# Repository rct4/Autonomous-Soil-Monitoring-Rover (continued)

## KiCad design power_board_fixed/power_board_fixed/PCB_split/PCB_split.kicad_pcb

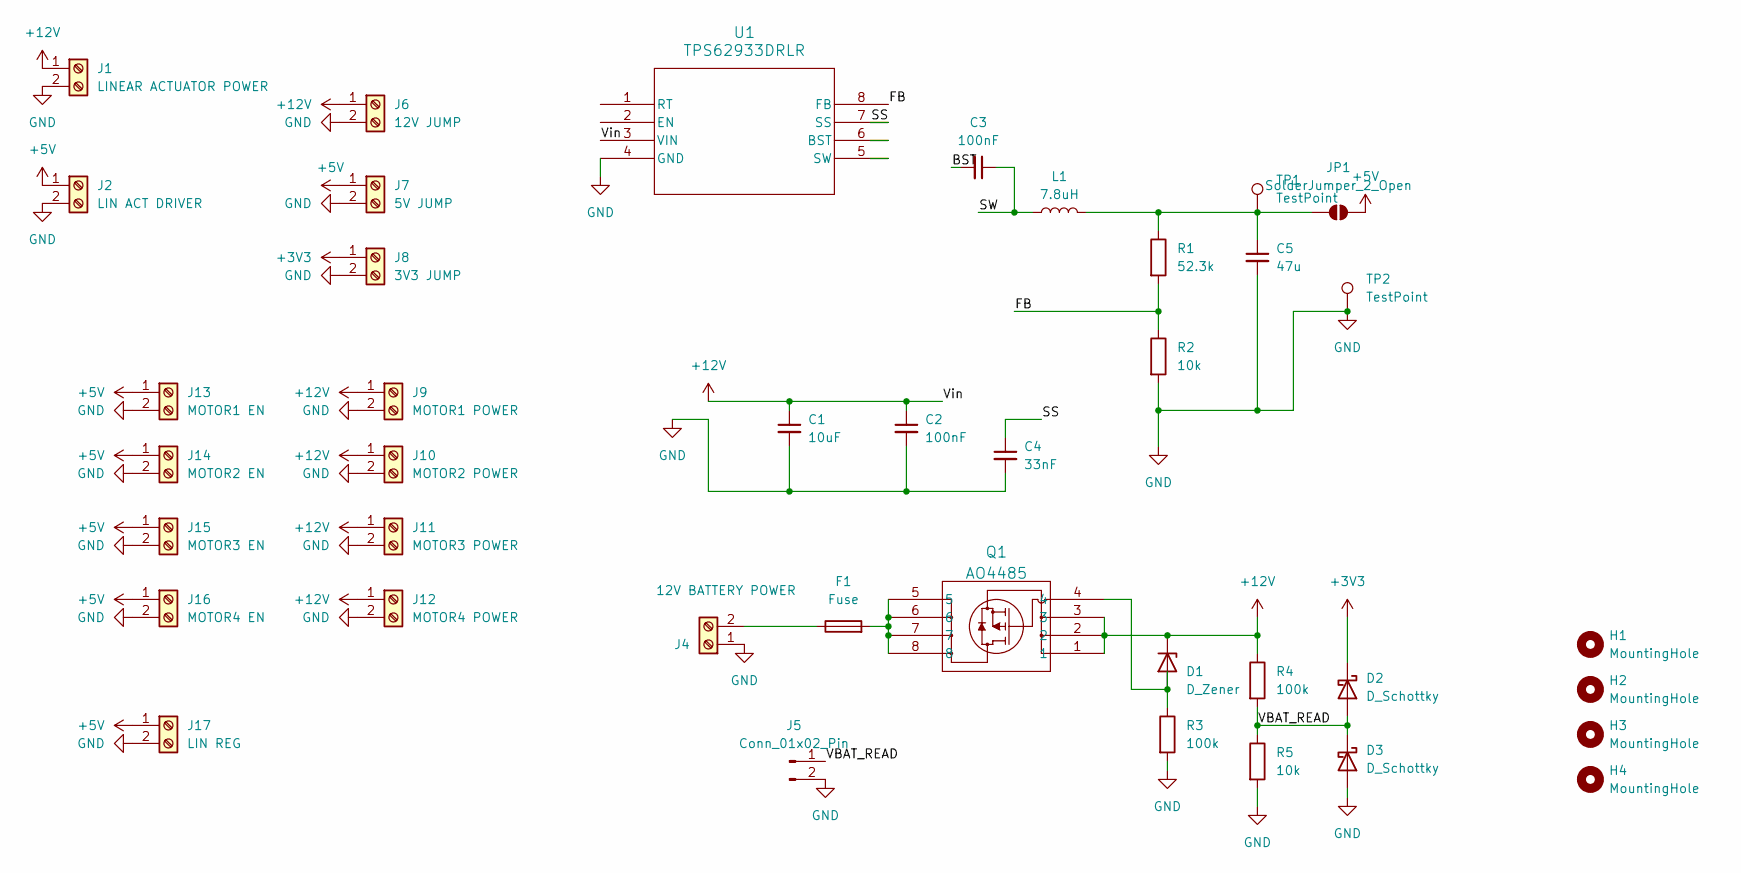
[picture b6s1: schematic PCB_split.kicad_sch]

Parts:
C1: 10uF; C_0805_2012Metric_Pad1.18x1.45mm_HandSolder
C2, C3: 100nF; C_0805_2012Metric_Pad1.18x1.45mm_HandSolder
C4: 33nF; C_0805_2012Metric_Pad1.18x1.45mm_HandSolder
C5: 47u; C_0805_2012Metric_Pad1.18x1.45mm_HandSolder
D1: D_Zener; D_SOD-123
D2, D3: D_Schottky; TSOT-23_HandSoldering
F1: Fuse; Fuseholder_Littelfuse_Nano2_154x
H1, H2, H3, H4: MountingHole; MountingHole_3.2mm_M3
J1: LINEAR ACTUATOR POWER; TerminalBlock_Phoenix_MKDS-1,5-2-5.08_1x02_P5.08mm_Horizont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
J2: LIN ACT DRIVER; TerminalBlock_Phoenix_MKDS-1,5-2-5.08_1x02_P5.08mm_Horizont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
J4: 12V BATTERY POWER; TerminalBlock_Phoenix_MKDS-1,5-2-5.08_1x02_P5.08mm_Horizont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
J5: Conn_01x02_Pin; TerminalBlock_Phoenix_MKDS-1,5-2-5.08_1x02_P5.08mm_Horizont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
J6: 12V JUMP; TerminalBlock_Phoenix_MKDS-1,5-2-5.08_1x02_P5.08mm_Horizont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
J7: 5V JUMP; TerminalBlock_Phoenix_MKDS-1,5-2-5.08_1x02_P5.08mm_Horizont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
J8: 3V3 JUMP; TerminalBlock_Phoenix_MKDS-1,5-2-5.08_1x02_P5.08mm_Horizont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
J9: MOTOR1 POWER; TerminalBlock_Phoenix_MKDS-1,5-2-5.08_1x02_P5.08mm_Horizont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
J10: MOTOR2 POWER; TerminalBlock_Phoenix_MKDS-1,5-2-5.08_1x02_P5.08mm_Horizont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
J11: MOTOR3 POWER; TerminalBlock_Phoenix_MKDS-1,5-2-5.08_1x02_P5.08mm_Horizont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
J12: MOTOR4 POWER; TerminalBlock_Phoenix_MKDS-1,5-2-5.08_1x02_P5.08mm_Horizont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
J13: MOTOR1 EN; TerminalBlock_Phoenix_MKDS-1,5-2-5.08_1x02_P5.08mm_Horizont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
J14: MOTOR2 EN; TerminalBlock_Phoenix_MKDS-1,5-2-5.08_1x02_P5.08mm_Horizont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
J15: MOTOR3 EN; TerminalBlock_Phoenix_MKDS-1,5-2-5.08_1x02_P5.08mm_Horizont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
J16: MOTOR4 EN; TerminalBlock_Phoenix_MKDS-1,5-2-5.08_1x02_P5.08mm_Horizont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
J17: LIN REG; TerminalBlock_Phoenix_MKDS-1,5-2-5.08_1x02_P5.08mm_Horizont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
JP1: SolderJumper_2_Open; SolderJumper-2_P1.3mm_Open_RoundedPad1.0x1.5mm
L1: 7.8uH; L_0201_0603Metric_Pad0.64x0.40mm_HandSolder
Q1: AO4485; SO8SOP-8L_AOS
R1: 52.3k; R_0805_2012Metric_Pad1.20x1.40mm_HandSolder
R2, R5: 10k; R_0805_2012Metric_Pad1.20x1.40mm_HandSolder
R3, R4: 100k; R_0805_2012Metric_Pad1.20x1.40mm_HandSolder
TP1, TP2: TestPoint; TestPoint_Pad_2.5x2.5mm
U1: TPS62933DRLR; SOT5X3-8_DRL_TEX

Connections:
+3V3: D2.1 (K), J8.1
+5V: J2.1, J7.1, J13.1, J14.1, J15.1, J16.1, J17.1, JP1.2 (B)
+12V: C1.1, C2.1, D1.1 (K), J1.1, J6.1, J9.1, J10.1, J11.1, J12.1, Q1.1, Q1.2, Q1.3, R4.1, U1.3 (VIN)
/BST: C3.2
/FB: R1.2, R2.1, U1.8 (FB)
/SS: C4.1, U1.7 (SS)
/SW: C3.1, L1.1
/VBAT_READ: D2.2 (A), D3.1 (K), J5.1, R4.2, R5.1
GND: C1.2, C2.2, C4.2, C5.2, D3.2 (A), J1.2, J2.2, J4.1, J5.2, J6.2, J7.2, J8.2, J9.2, J10.2, J11.2, J12.2, J13.2, J14.2, J15.2, J16.2, J17.2, R2.2, R3.2, R5.2, TP2.1, U1.4 (GND)
unnamed: D1.2 (A), Q1.4, R3.1
unnamed: F1.2, Q1.5, Q1.6, Q1.7, Q1.8
unnamed: F1.1, J4.2
unnamed: C5.1, JP1.1 (A), L1.2, R1.1, TP1.1

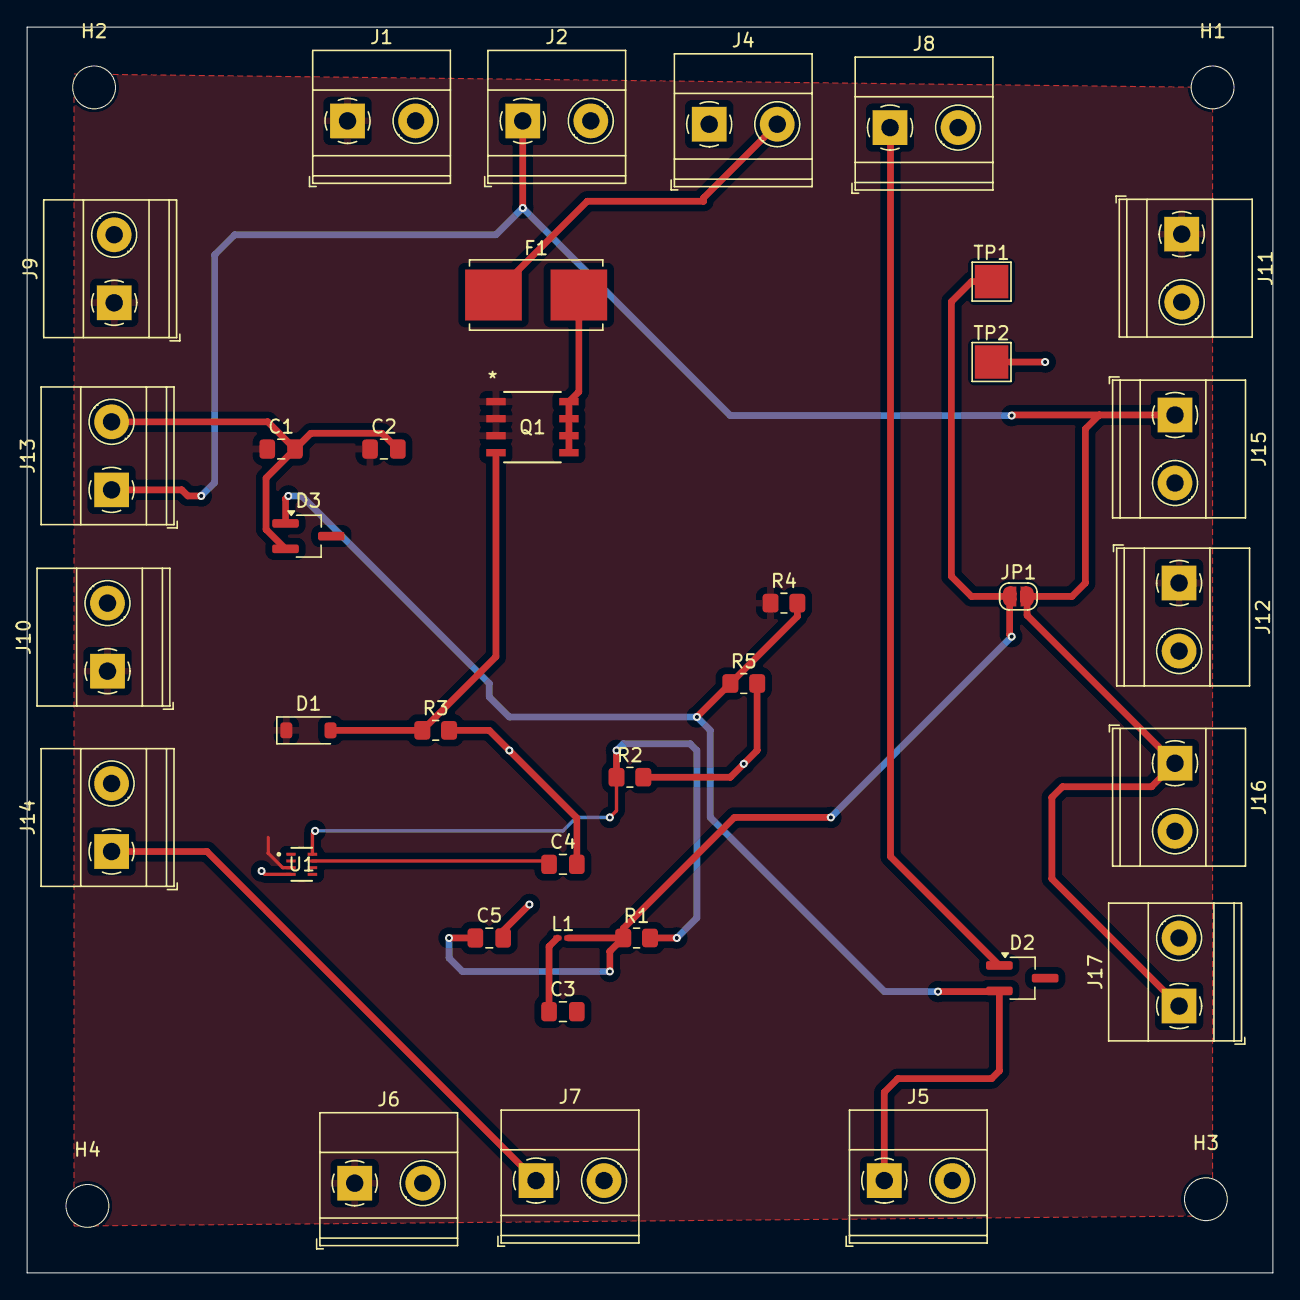
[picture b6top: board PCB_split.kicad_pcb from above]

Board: 2 copper layers, 93.0 x 93.0 mm, 40 parts (0 on the bottom side), 12 nets.

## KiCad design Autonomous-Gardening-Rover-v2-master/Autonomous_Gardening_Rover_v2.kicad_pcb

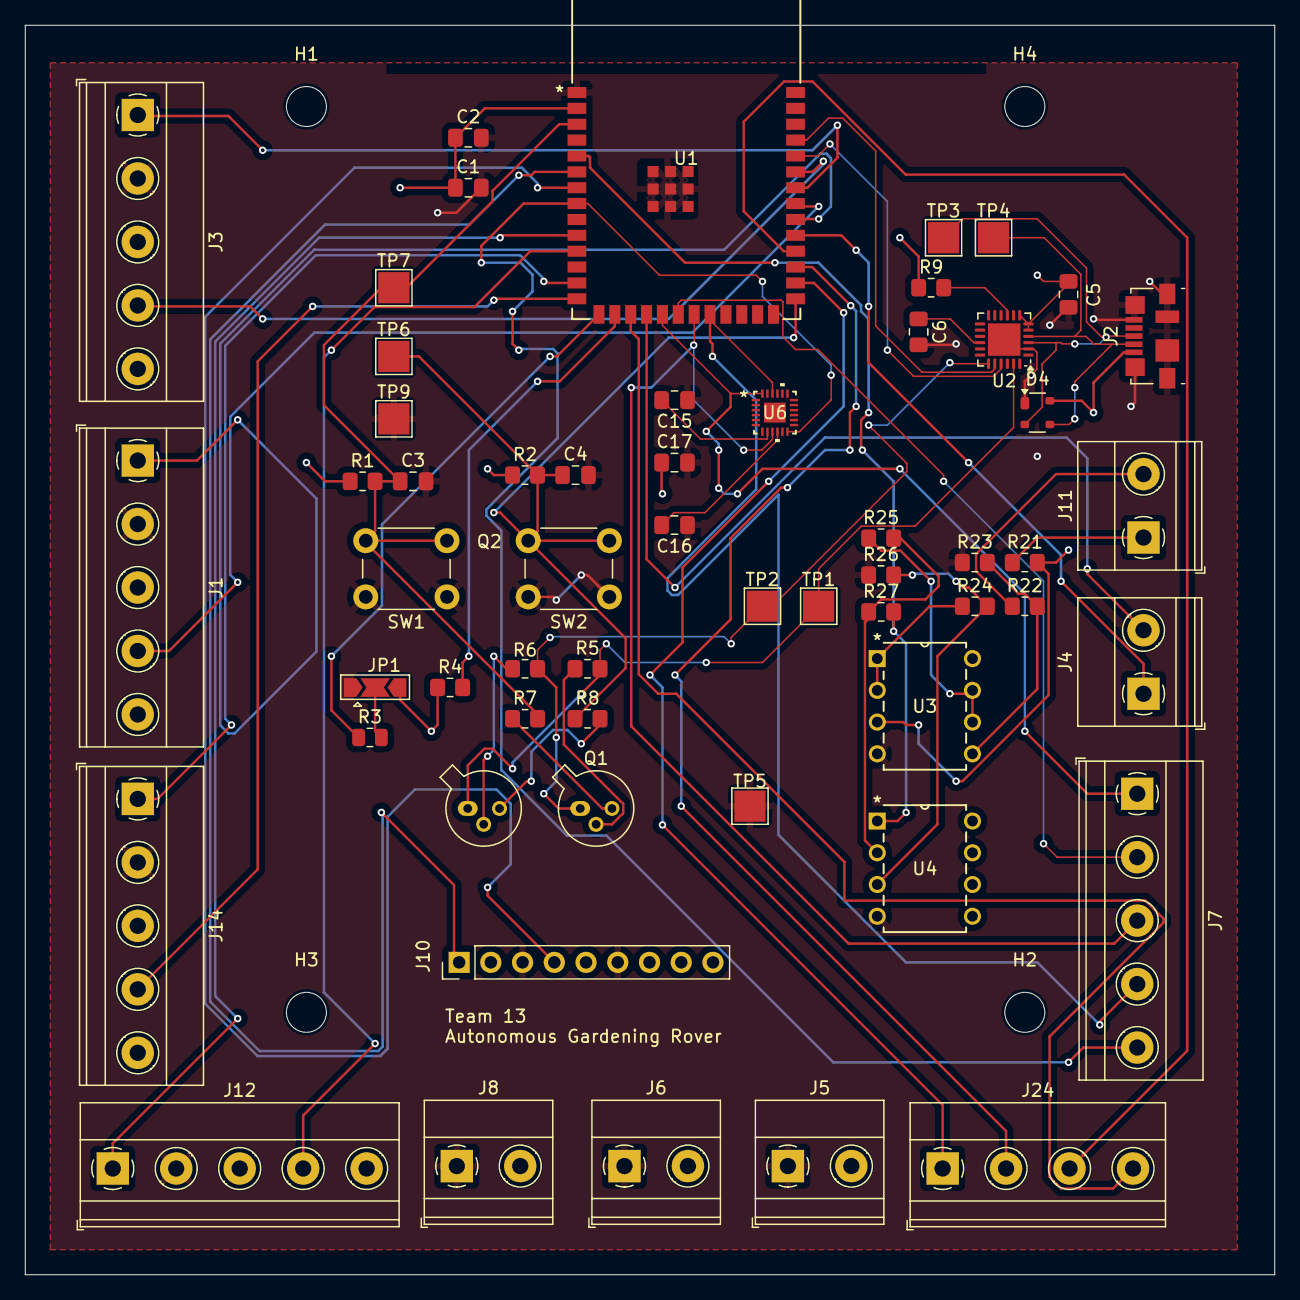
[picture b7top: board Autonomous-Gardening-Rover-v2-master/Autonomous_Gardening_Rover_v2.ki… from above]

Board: 6 copper layers, 100.0 x 100.0 mm, 61 parts (0 on the bottom side), 51 nets.

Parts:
C1: 10 uF; C_0805_2012Metric_Pad1.18x1.45mm_HandSolder
C2: 100 uF; C_0805_2012Metric_Pad1.18x1.45mm_HandSolder
C3, C4: 1 uF; C_0805_2012Metric_Pad1.18x1.45mm_HandSolder
C5: 10uF; C_0805_2012Metric_Pad1.18x1.45mm_HandSolder
C6: 4.7uF; C_0805_2012Metric_Pad1.18x1.45mm_HandSolder
C15: 10nf; C_0805_2012Metric_Pad1.18x1.45mm_HandSolder
C16, C17: 0.1uf; C_0805_2012Metric_Pad1.18x1.45mm_HandSolder
D4: SP0503BAHT; SOT-143
H1, H2, H3, H4: MountingHole; MountingHole_3.2mm_M3
J1, J3, J12, J14: Conn_01x05_Pin; TerminalBlock_Phoenix_MKDS-1,5-5-5.08_1x05_P5.08mm_Horizont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
J2: USB_B_Micro; USB_Micro-B_Molex_47346-0001
J4: LINEAR ACTUATOR SIGNAL; TerminalBlock_Phoenix_MKDS-1,5-2-5.08_1x02_P5.08mm_Horizont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
J5, J6, J8: Screw_Terminal_01x02; TerminalBlock_Phoenix_MKDS-1,5-2-5.08_1x02_P5.08mm_Horizont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
J7: MPU SIGNAL; TerminalBlock_Phoenix_MKDS-1,5-5-5.08_1x05_P5.08mm_Horizont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
J10: SENSORS; PinHeader_1x09_P2.54mm_Vertical
J11: Conn_01x02_Socket; TerminalBlock_Phoenix_MKDS-1,5-2-5.08_1x02_P5.08mm_Horizont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
J24: UWB SIGNAL; TerminalBlock_Phoenix_MKDS-1,5-4-5.08_1x04_P5.08mm_Horizont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
JP1: SolderJumper_3_Open; SolderJumper-3_P2.0mm_Open_TrianglePad1.0x1.5mm
Q1, Q2: BC107; TO-18-3
R1, R2: 100k; R_0805_2012Metric_Pad1.20x1.40mm_HandSolder
R3: 1k; R_0805_2012Metric
R4: 1k; R_0805_2012Metric_Pad1.20x1.40mm_HandSolder
R5, R6, R7, R8: 10k; R_0805_2012Metric_Pad1.20x1.40mm_HandSolder
R9: 4.7k; R_0805_2012Metric_Pad1.20x1.40mm_HandSolder
R21, R22: 100K; R_0805_2012Metric_Pad1.20x1.40mm_HandSolder
R23: 10M; R_0805_2012Metric_Pad1.20x1.40mm_HandSolder
R24, R25, R26, R27: 1K; R_0805_2012Metric_Pad1.20x1.40mm_HandSolder
SW1, SW2: SW_Push; SW_PUSH_6mm_H5mm
TP1, TP2, TP3, TP4, TP5: TestPoint; TestPoint_Pad_2.5x2.5mm
TP6: TEST GPIO0_STRAPPING; TestPoint_Pad_2.5x2.5mm
TP7: TEST CHIP_PU; TestPoint_Pad_2.5x2.5mm
TP9: TEST GND; TestPoint_Pad_2.5x2.5mm
U1: ESP32-S3-WROOM-1; ESP32-S3-WROOM-1_EXP
U2: CP2104; QFN-24-1EP_4x4mm_P0.5mm_EP2.6x2.6mm
U3, U4: LM358; P8
U6: MPU-6500; QFN24_3X3X0P9_IVS

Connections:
+3V3: C1.1, C2.1, C5.1, C15.2, C17.1, J8.2, J10.2, J10.5, JP1.3 (B), R1.1, R2.1, R4.1, R9.1, R21.2, U1.2 (3V3), U2.5 (VIO), U2.6 (VDD), U2.7 (REGIN), U3.3 (+), U3.8 (V+), U4.8 (V+), U6.8 (VDDIO), U6.13 (VDD)
+5V: D4.4 (K), J1.3, J2.1 (VBUS), J3.3, J6.2, J12.3, J14.3
+12V: J1.5, J3.5, J5.2, J12.5, J14.5
/CHIP_PU: C3.1, R1.2, R7.2, SW1.2, TP7.1, U1.3 (EN)
/D+: D4.2 (K), J2.3 (D+), TP3.1, U2.3 (D+)
/D-: D4.3 (K), J2.2 (D-), TP4.1, U2.4 (D-)
/DTR: Q2.1 (E), R5.2, TP1.1, U2.23 (~DTR)
/GPIO0_STRAPPING: C4.1, R2.2, R8.1, SW2.2, TP6.1, U1.27 (IO0)
/GPIO3_STRAPPING: R3.1, U1.15 (IO3)
/GPIO46_STRAPPING: R4.2, U1.16 (IO46)
/Input_Probe_1: J11.1, R21.1
/Input_Probe_2: J11.2, R22.1
/LINACT+: J4.1, U1.31 (IO38)
/LINACT-: J4.2, U1.18 (IO10)
/MOTOR1FG: J12.4, U1.11 (IO18)
/MOTOR1PWM: J12.1, U1.10 (IO17)
/MOTOR2FG: J14.4, U1.14 (IO20)
/MOTOR2PWM: J14.1, U1.13 (IO19)
/MOTOR3FG: J1.4, U1.33 (IO40)
/MOTOR3PWM: J1.1, U1.32 (IO39)
/MOTOR4FG: J3.4, U1.35 (IO42)
/MOTOR4PWM: J3.1, U1.34 (IO41)
/MPUCLK: J7.2, U1.20 (IO12), U6.23 (SCL/SCLK)
/MPUCS: J7.4, U1.22 (IO14), U6.22 (nCS)
/MPUINT: J7.5, U1.8 (IO15), U6.12 (INT)
/MPUMISO: J7.3, U1.21 (IO13), U6.9 (SDO/ADO)
/MPUMOSI: J7.1, U1.19 (IO11), U6.24 (SDA/SDI)
/Moisture_Sensor_Output: R27.2, U1.5 (IO5), U4.1
/RTS: Q1.1 (E), R6.2, TP2.1, U2.19 (~RTS)
/RXD: U1.37 (TXD0), U2.20 (RXD)
/TXD: U1.36 (RXD0), U2.21 (TXD)
/UWBCLK: J24.2, U1.29 (IO36)
/UWBCS: J24.4, U1.17 (IO9)
/UWBMISO: J24.3, U1.30 (IO37)
/UWBMOSI: J24.1, U1.28 (IO35)
/pH_Sensor: J10.1, U1.6 (IO6)
/temp_Sensor: J10.4, U1.7 (IO7)
GND: C1.2, C2.2, C3.2, C4.2, C5.2, C6.2, C15.1, C16.1, C17.2, D4.1 (A), J1.2, J2.5 (GND), J2.6 (Shield), J3.2, J5.1, J6.1, J8.1, J10.3, J10.6, J12.2, J14.2, JP1.1 (A), R23.1, R26.1, SW1.1, SW2.1, TP5.1, TP9.1, U1.1 (GND), U1.40 (GND), U1.41 (GND), U2.2 (GND), U2.25 (GND), U3.4 (V-), U4.4 (V-), U6.18 (GND)
unnamed: JP1.2 (C), R3.2
unnamed: Q1.2 (B), R5.1
unnamed: Q1.3 (C), R7.1
unnamed: Q2.2 (B), R6.1
unnamed: Q2.3 (C), R8.2
unnamed: C6.1, U2.16 (VPP)
unnamed: R9.2, U2.9 (~RST)
unnamed: R24.1, U3.1, U3.2 (-)
unnamed: R22.2, R23.2, U3.5 (+)
unnamed: R25.1, U3.6 (-), U3.7
unnamed: R24.2, R26.2, U4.3 (+)
unnamed: R25.2, R27.1, U4.2 (-)
unnamed: C16.2, U6.10 (REGOUT)

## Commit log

2024-10-08 Add schematics
2024-10-08 Add PCB PDF
2024-10-08 Add image
2024-10-08 Update PCB
2024-10-08 Update buck converter
2024-10-11 Add linear regulator
2024-10-11 Add moisture sensor
2024-10-21 Add V2
2024-10-28 Add png
2024-10-29 Update PCBS
2024-11-09 Update V4
2024-11-11 New version
2024-11-23 Add V7
2024-11-24 Finish v7 pcb
2024-11-24 Final V7
2024-12-15 Restructure
2024-12-16 Push software
